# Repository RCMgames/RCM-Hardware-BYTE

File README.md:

# RCM-Hardware-BYTE
v2.3

* 1.25 by 1.25 inches, 31.75 by 31.75 millimeters
* 8 motors
* 8 servos
* battery monitoring
* I2C connector on QT PY
* runs on 3-11 volts

### Tested with the following types of ESP32 QT Py:
| Type of Qt Py | PlatformIO name | link to Adafruit |
| ------ | -------- | -------- |
| S3 with 2MB PSRAM |  adafruit_qtpy_esp32s3_n4r2   |  https://www.adafruit.com/product/5700   |
| S3 with 8Mb Flash |  adafruit_qtpy_esp32s3_nopsram   |  https://www.adafruit.com/product/5426   |
| S2 |  adafruit_qtpy_esp32s2   |  https://www.adafruit.com/product/5325  |

Look here for how to program it: https://github.com/RCMgames/RCMv2

Look here for more information and examples of robots: https://github.com/rcmgames

Want slightly smaller with a built in IMU? Look at the [Nibble](https://github.com/RCMgames/RCM-Hardware-Nibble)

## Options for purchasing

* [PCBWay link](https://www.pcbway.com/project/shareproject/RCMHardwareByte_v2_3_e23eec63.html) (PCBWay will give me a commission without increasing the price for you). (approximately $90 for 2 boards and manufacturing took a month).
* send the gerbers, bill of materials, and ComponentPlacement files to a PCB manufacturer of your choice (details you may be asked for: min hole 0.25mm, min track/spacing 5/5mil, thickness 1.0mm, 1 oz Cu outer 1.5 oz Cu inner)

## Components
Solder by hand to complete the assembly of your boards.
| part | links | quantity | notes |
| ----- | ----- | ----- | ----- |
| RCM BYTE circuit board | [options for purchasing](https://github.com/RCMgames/RCM-Hardware-BYTE/tree/main#options-for-purchasing) | 1 | |
| ESP32 QT Py | [compatible QT Py](https://github.com/RCMgames/RCM-Hardware-BYTE/tree/main#tested-with-the-following-types-of-esp32-qt-py) | 1 | |
| 2x8 female header pins | [this](https://www.digikey.com/en/products/detail/sullins-connector-solutions/PPPC042LFBN-RC/810244) or 2 strips of 8 | 1 | for motors |
| 7 female header pins | | 2 | for QT Py |
| 8 male header pins | | 4 | for servos |
| battery wires | JST RCY OR 9V battery snap | 1 | [Amazon JST RCY](https://www.amazon.com/dp/B00Z04QFN2/) |
| servo buck boost 5v 2A OR replace with a short length of wire| [Pololu](https://www.pololu.com/product/4085) | 2 | regulators are needed if you want to supply voltages above or below what servos can accept. There are 2 servo power buses, each with 4 servos. |

## Acknowledgements
* I would like to thank [PCBWay](https://www.pcbway.com/) for sponsoring prototyping runs of this project. PCBWay produces very nice boards, supports open source hardware, and gave me great support as I worked on this project. Special thanks to Liam!

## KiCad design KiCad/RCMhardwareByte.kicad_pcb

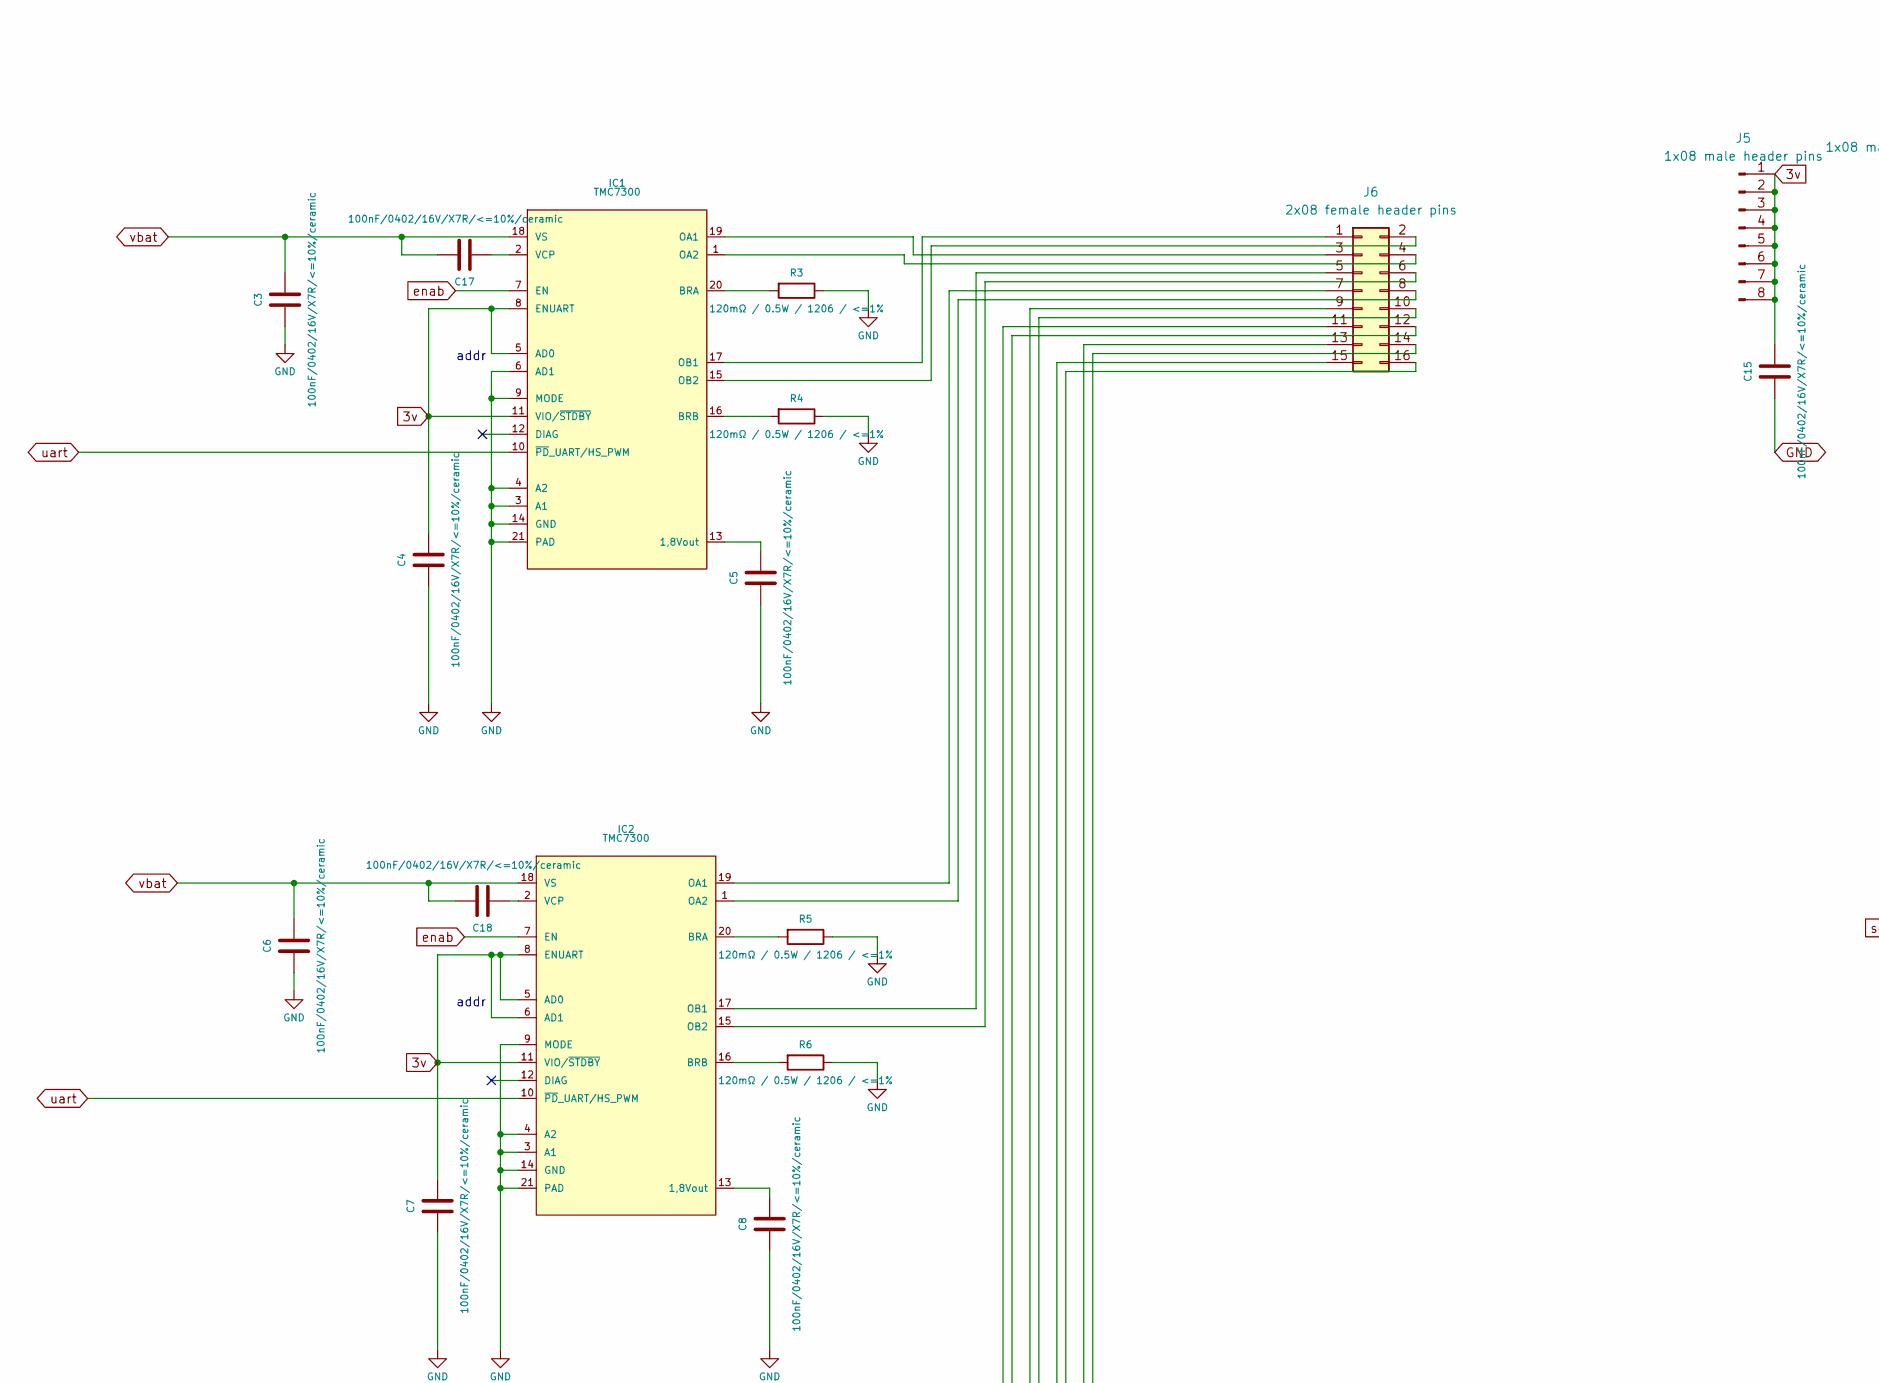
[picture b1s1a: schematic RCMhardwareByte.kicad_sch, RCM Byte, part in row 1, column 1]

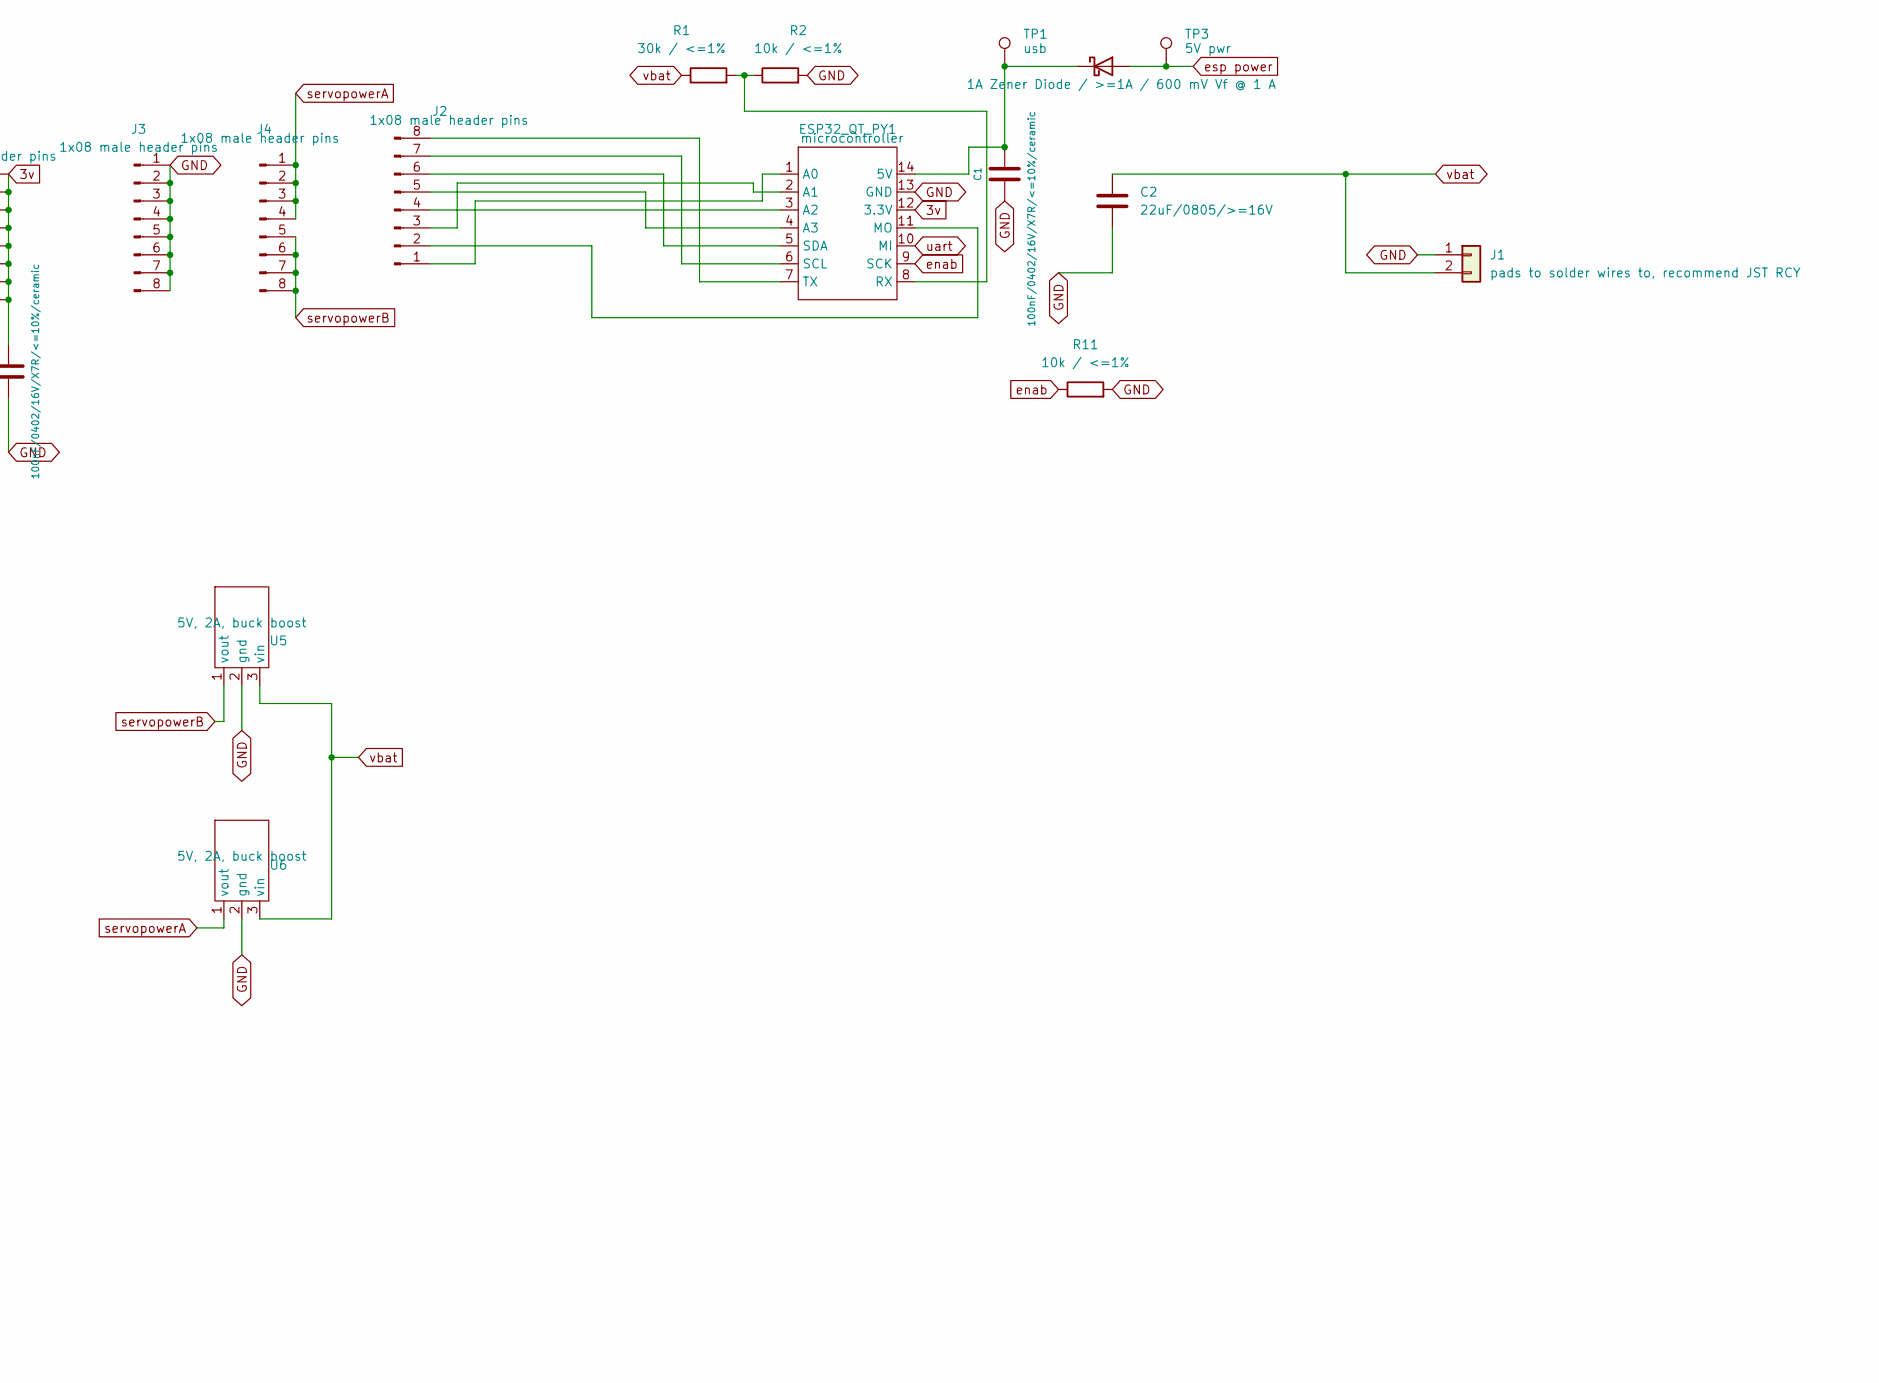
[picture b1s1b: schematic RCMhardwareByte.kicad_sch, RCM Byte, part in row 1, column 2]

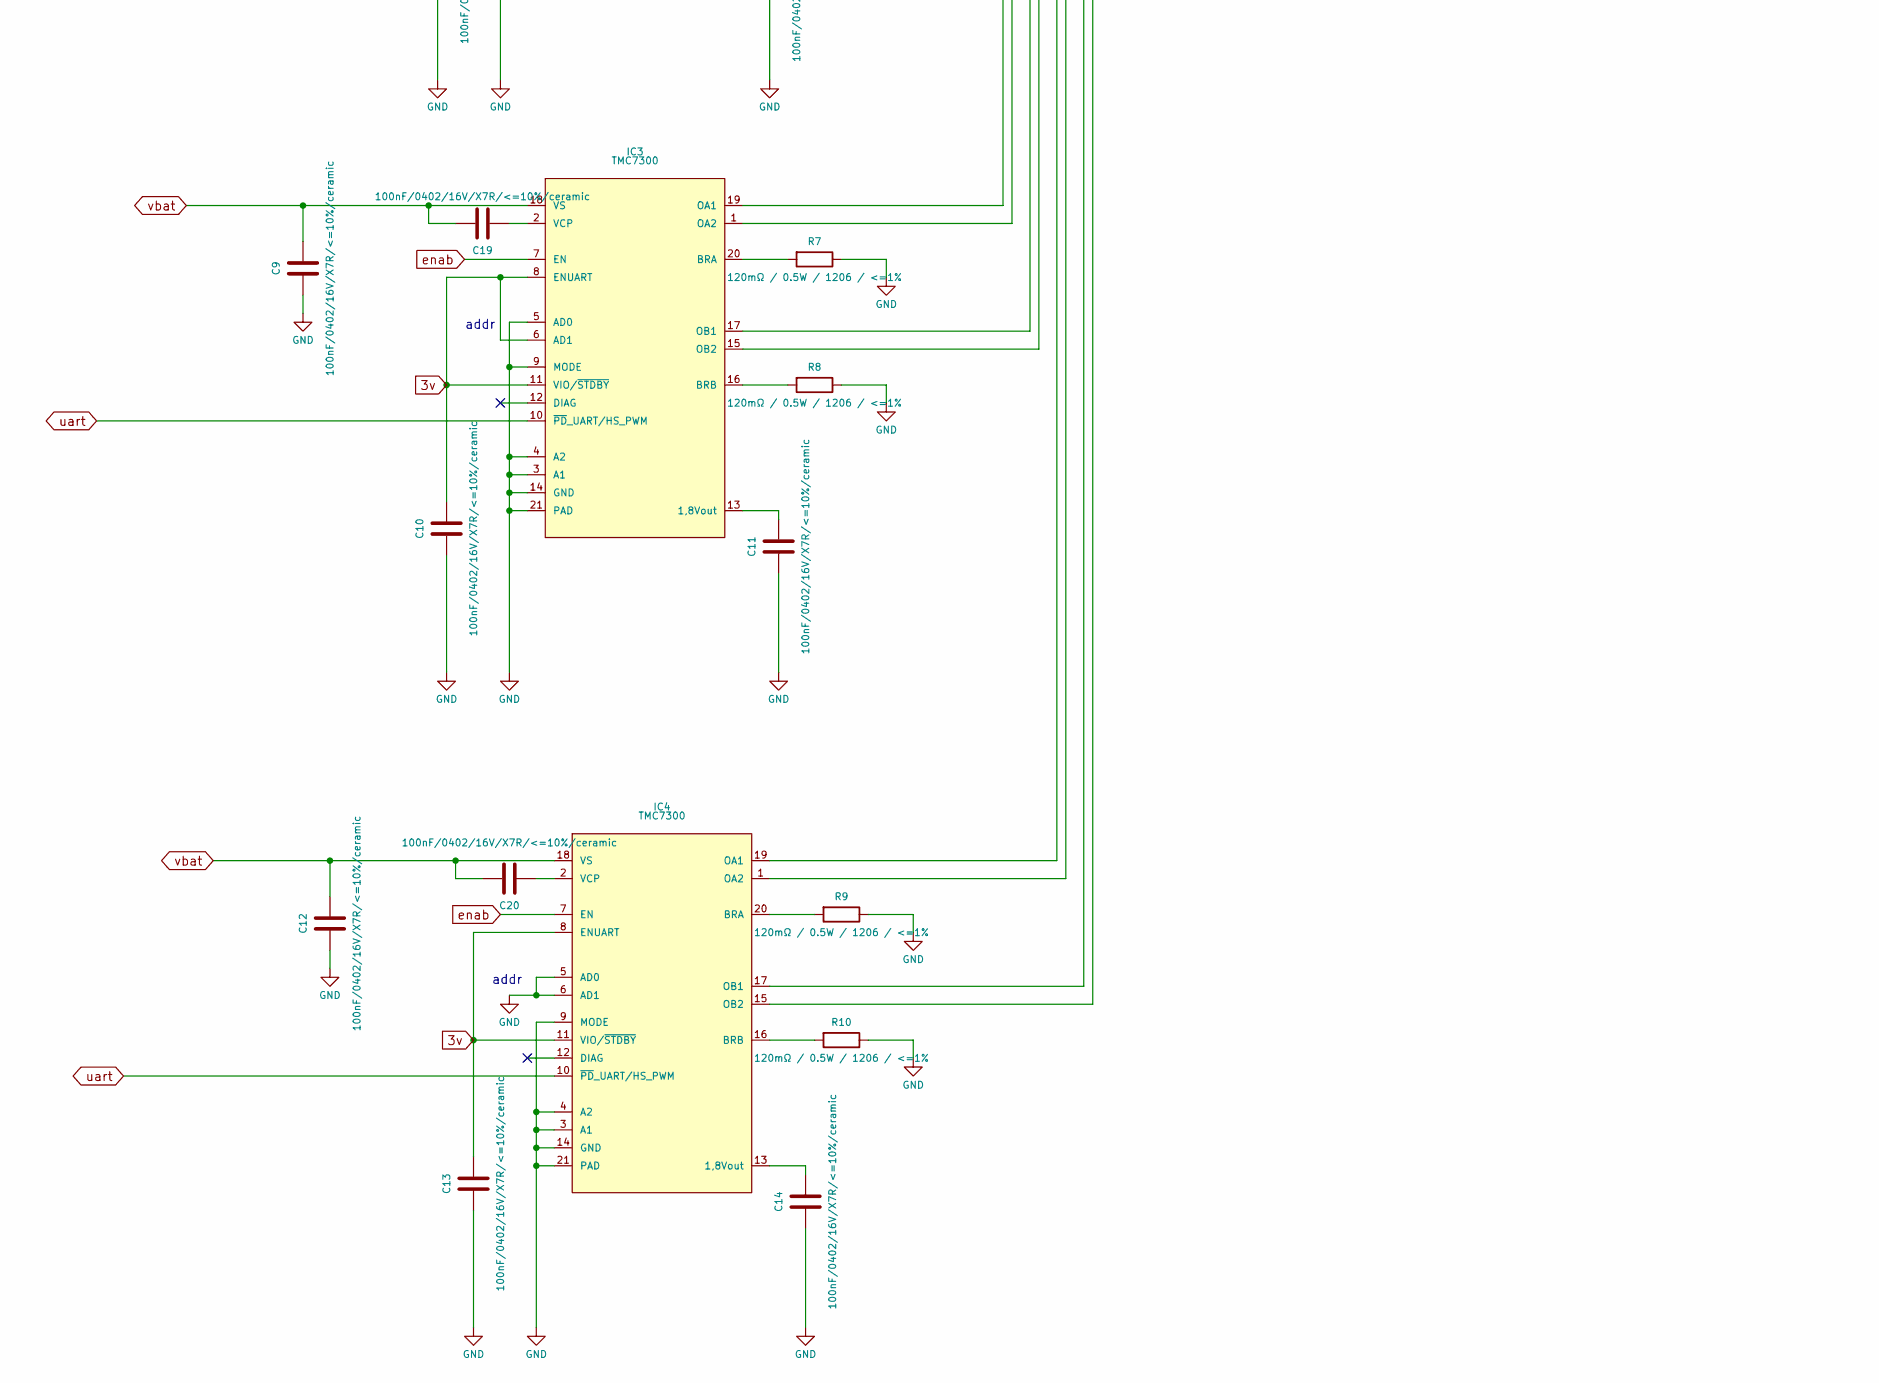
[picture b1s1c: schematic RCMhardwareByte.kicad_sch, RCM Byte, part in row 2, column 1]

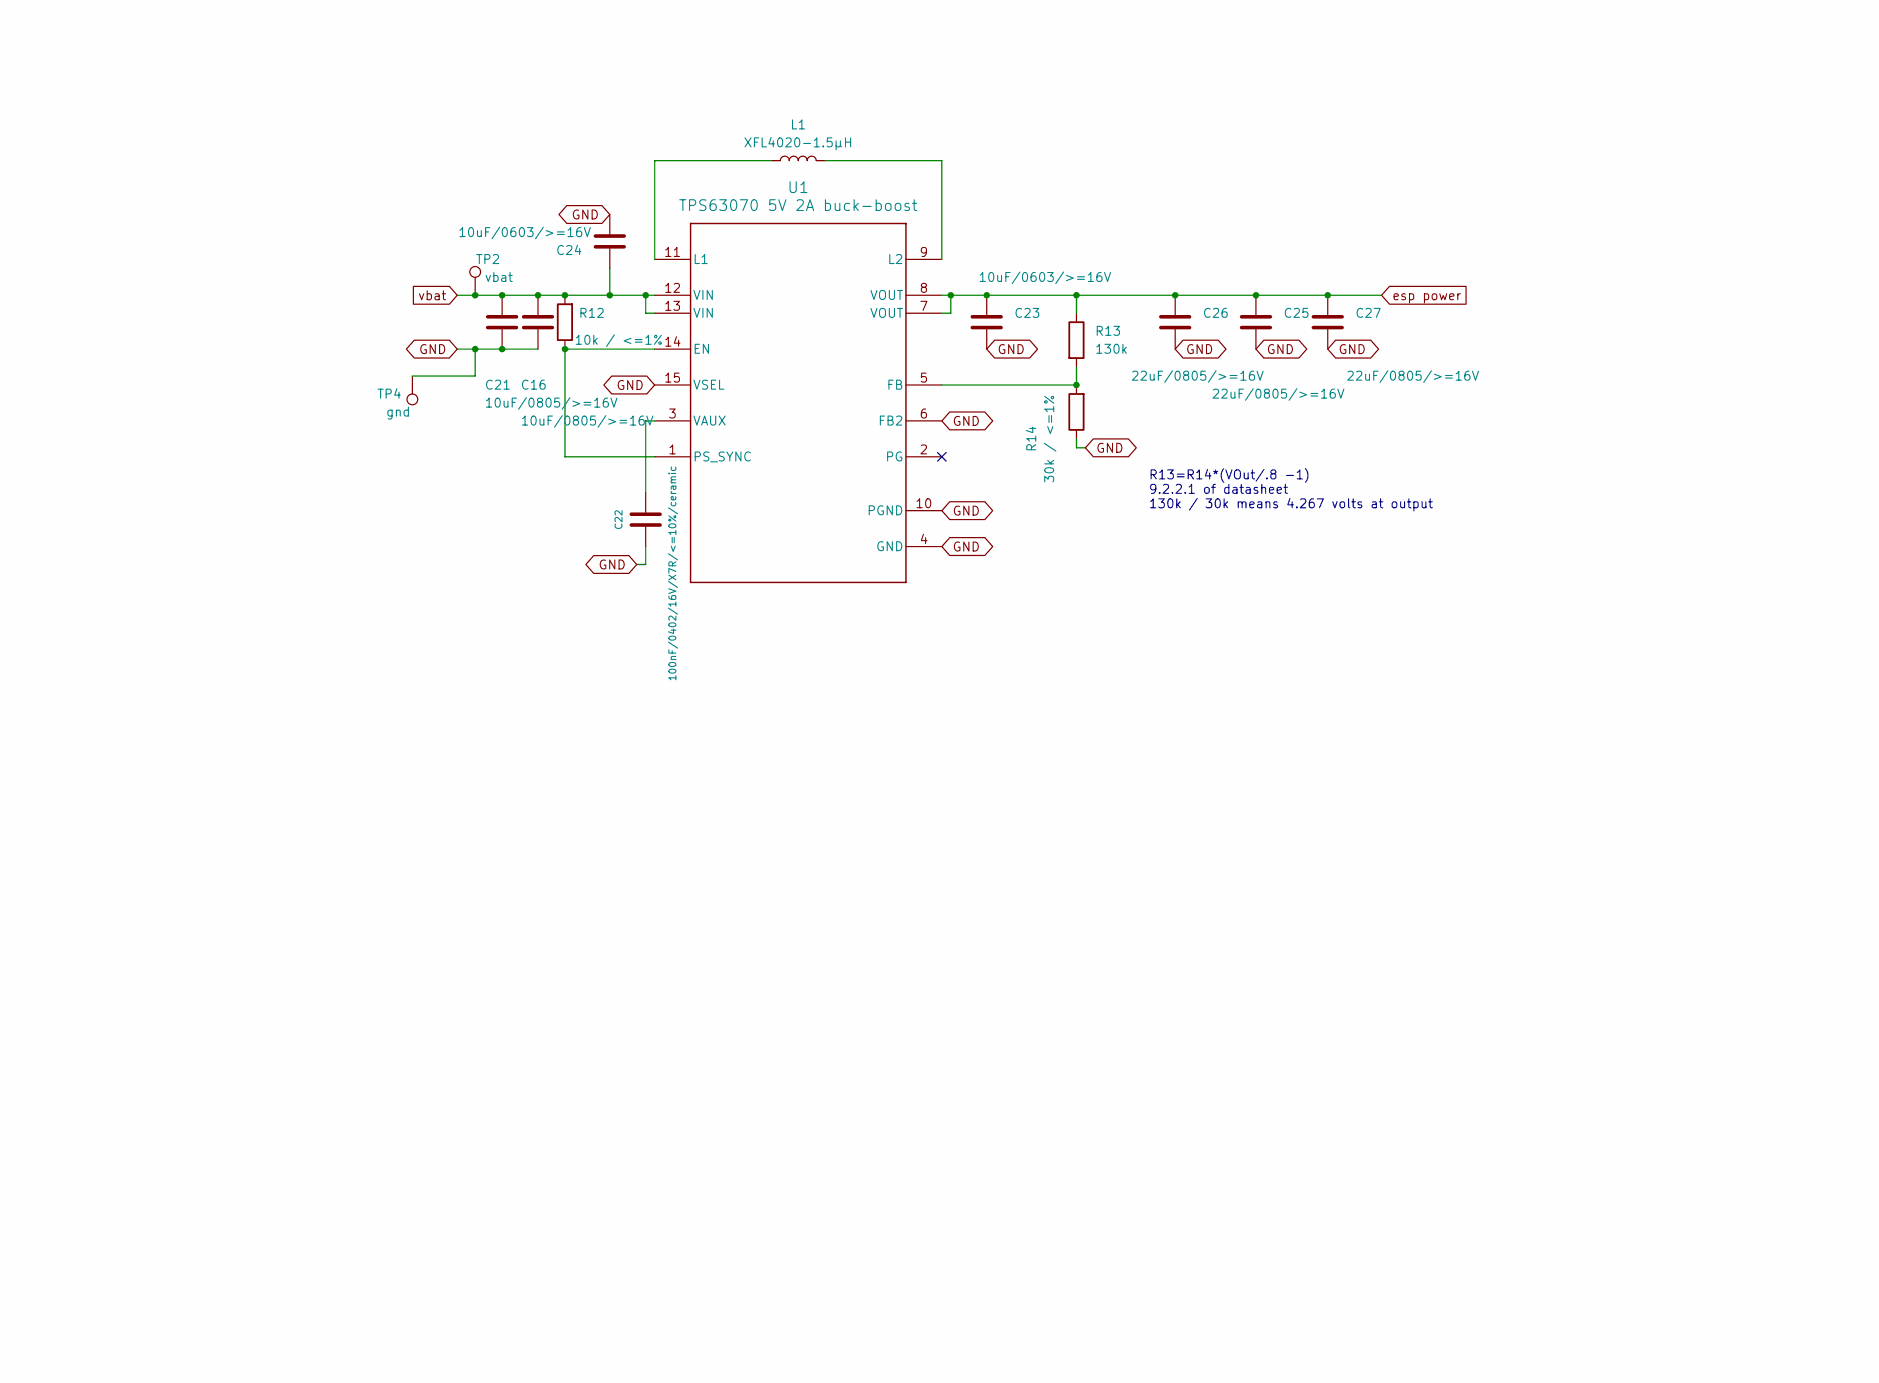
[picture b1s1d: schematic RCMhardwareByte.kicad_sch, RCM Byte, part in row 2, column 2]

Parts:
C1, C3, C4, C5, C6, C7, C8, C9, C10, C11, C12, C13, C14, C15, C17, C18, C19, C20, C22: 100nF/0402/16V/X7R/<=10%/ceramic; C_0402_1005Metric; mpn GMC04X7R104K50NT; digikey part # 4713-GMC04X7R104K50NTCT-ND
C2, C25, C26, C27: 22uF/0805/>=16V; C_0805_2012Metric; mpn GMC21X5R226M16NT; digikey part # 4713-GMC21X5R226M16NTCT-ND
C16, C21: 10uF/0805/>=16V; C_0805_2012Metric; mpn GMC21X7R106K16NT; digikey part # 4713-GMC21X7R106K16NTCT-ND
C23, C24: 10uF/0603/>=16V; C_0603_1608Metric; mpn GMC10X5R106M25NT; digikey part # 4713-GMC10X5R106M25NTCT-ND
D1: 1A Zener Diode / >=1A / 600 mV Vf @ 1 A; D_SOD-323; mpn GDB5818WS; digikey part # 4786-GDB5818WSCT-ND
ESP32_QT_PY1: microcontroller; ESP32 QT PY
IC1, IC2, IC3, IC4: TMC7300; QFN-20-1EP_3x3mm_P0.4mm_EP1.65x1.65mm; mpn TMC7300-LA-T; digikey part # 175-TMC7300-LA-TCT-ND
J1: pads to solder wires to, recommend JST RCY; battery wires
J2, J3, J4, J5: 1x08 male header pins; servo pin column
J6: 2x08 female header pins; PinSocket_2x08_P2.54mm_Vertical
L1: XFL4020-1.5μH; L_Coilcraft_XxL4020; mpn XFL4020-152MEC; digikey part # 2457-XFL4020-152MEC-ND
R1, R14: 30k / <=1%; R_0402_1005Metric; mpn CRG0402F30K; digikey part # 1712-CRG0402F30KCT-ND
R2, R11, R12: 10k / <=1%; R_0402_1005Metric; mpn CRG0402F10K; digikey part # A121528CT-ND
R3, R4, R5, R6, R7, R8, R9, R10: 120mΩ / 0.5W / 1206 / <=1%; R_1206_3216Metric; mpn CRL1206-FW-R120ELF; digikey part # CRL1206-FW-R120ELFCT-ND
R13: 130k; R_0402_1005Metric; mpn CPF0402B130KE; digikey part # A119923CT-ND
TP1: usb; TestPoint_Pad_D1.5mm; mpn n/a; digikey part # n/a
TP2: vbat; TestPoint_Pad_D1.5mm; mpn n/a; digikey part # n/a
TP3: 5V pwr; TestPoint_Pad_D1.5mm; mpn n/a; digikey part # n/a
TP4: gnd; TestPoint_Pad_D1.5mm; mpn n/a; digikey part # n/a
U1: TPS63070 5V 2A buck-boost; TPS630701RNMR; mpn TPS63070RNMR; digikey part # 296-44874-1-ND
U5, U6: 5V, 2A, buck boost; pololu4085

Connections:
3v: C4.1, C7.1, C10.1, C13.1, C15.1, ESP32_QT_PY1.12 (3.3V), IC1.5 (AD0), IC1.8 (ENUART), IC1.11 (VIO/~STDBY), IC2.5 (AD0), IC2.6 (AD1), IC2.8 (ENUART), IC2.11 (VIO/~STDBY), IC3.6 (AD1), IC3.8 (ENUART), IC3.11 (VIO/~STDBY), IC4.8 (ENUART), IC4.11 (VIO/~STDBY), J5.1, J5.2, J5.3, J5.4, J5.5, J5.6, J5.7, J5.8
GND: C1.2, C2.2, C3.2, C4.2, C5.2, C6.2, C7.2, C8.2, C9.2, C10.2, C11.2, C12.2, C13.2, C14.2, C15.2, C16.2, C21.2, C22.2, C23.2, C24.2, C25.2, C26.2, C27.2, ESP32_QT_PY1.13 (GND), IC1.3 (A1), IC1.4 (A2), IC1.6 (AD1), IC1.9 (MODE), IC1.14 (GND), IC1.21 (PAD), IC2.3 (A1), IC2.4 (A2), IC2.9 (MODE), IC2.14 (GND), IC2.21 (PAD), IC3.3 (A1), IC3.4 (A2), IC3.5 (AD0), IC3.9 (MODE), IC3.14 (GND), IC3.21 (PAD), IC4.3 (A1), IC4.4 (A2), IC4.5 (AD0), IC4.6 (AD1), IC4.9 (MODE), IC4.14 (GND), IC4.21 (PAD), J1.1, J3.1, J3.2, J3.3, J3.4, J3.5, J3.6, J3.7, J3.8, R2.2, R3.1, R4.1, R5.1, R6.1, R7.1, R8.1, R9.1, R10.1, R11.2, R14.1, TP4.1, U1.4 (GND), U1.6 (FB2), U1.10 (PGND), U1.15 (VSEL), U5.2 (gnd), U6.2 (gnd)
unnamed: C1.1, D1.1 (K), ESP32_QT_PY1.14 (5V), TP1.1
unnamed: ESP32_QT_PY1.1 (A0), J2.1
unnamed: ESP32_QT_PY1.2 (A1), J2.3
unnamed: ESP32_QT_PY1.3 (A2), J2.4
unnamed: ESP32_QT_PY1.4 (A3), J2.5
unnamed: ESP32_QT_PY1.11 (MO), J2.2
unnamed: ESP32_QT_PY1.8 (RX), R1.2, R2.1
unnamed: ESP32_QT_PY1.6 (SCL), J2.7
unnamed: ESP32_QT_PY1.5 (SDA), J2.6
unnamed: ESP32_QT_PY1.7 (TX), J2.8
unnamed: C5.1, IC1.13 (1,8Vout)
unnamed: IC1.20 (BRA), R3.2
unnamed: IC1.16 (BRB), R4.2
unnamed: IC1.19 (OA1), J6.3
unnamed: IC1.1 (OA2), J6.4
unnamed: IC1.17 (OB1), J6.1
unnamed: IC1.15 (OB2), J6.2
unnamed: C17.2, IC1.2 (VCP)
unnamed: C8.1, IC2.13 (1,8Vout)
unnamed: IC2.20 (BRA), R5.2
unnamed: IC2.16 (BRB), R6.2
unnamed: IC2.19 (OA1), J6.7
unnamed: IC2.1 (OA2), J6.8
unnamed: IC2.17 (OB1), J6.5
unnamed: IC2.15 (OB2), J6.6
unnamed: C18.2, IC2.2 (VCP)
unnamed: C11.1, IC3.13 (1,8Vout)
unnamed: IC3.20 (BRA), R7.2
unnamed: IC3.16 (BRB), R8.2
unnamed: IC3.19 (OA1), J6.11
unnamed: IC3.1 (OA2), J6.12
unnamed: IC3.17 (OB1), J6.9
unnamed: IC3.15 (OB2), J6.10
unnamed: C19.2, IC3.2 (VCP)
unnamed: C14.1, IC4.13 (1,8Vout)
unnamed: IC4.20 (BRA), R9.2
unnamed: IC4.16 (BRB), R10.2
unnamed: IC4.19 (OA1), J6.15
unnamed: IC4.1 (OA2), J6.16
unnamed: IC4.17 (OB1), J6.13
unnamed: IC4.15 (OB2), J6.14
unnamed: C20.2, IC4.2 (VCP)
unnamed: R12.1, U1.1 (PS_SYNC), U1.14 (EN)
unnamed: R13.2, R14.2, U1.5 (FB)
unnamed: L1.1, U1.11 (L1)
unnamed: L1.2, U1.9 (L2)
unnamed: C22.1, U1.3 (VAUX)
enab: ESP32_QT_PY1.9 (SCK), IC1.7 (EN), IC2.7 (EN), IC3.7 (EN), IC4.7 (EN), R11.1
esp power: C23.1, C25.1, C26.1, C27.1, D1.2 (A), R13.1, TP3.1, U1.7 (VOUT), U1.8 (VOUT)
servopowerA: J4.1, J4.2, J4.3, J4.4, U6.1 (vout)
servopowerB: J4.5, J4.6, J4.7, J4.8, U5.1 (vout)
uart: ESP32_QT_PY1.10 (MI), IC1.10 (~PD_UART/HS_PWM), IC2.10 (~PD_UART/HS_PWM), IC3.10 (~PD_UART/HS_PWM), IC4.10 (~PD_UART/HS_PWM)
vbat: C2.1, C3.1, C6.1, C9.1, C12.1, C16.1, C17.1, C18.1, C19.1, C20.1, C21.1, C24.1, IC1.18 (VS), IC2.18 (VS), IC3.18 (VS), IC4.18 (VS), J1.2, R1.1, R12.2, TP2.1, U1.12 (VIN), U1.13 (VIN), U5.3 (vin), U6.3 (vin)

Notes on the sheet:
addr
R13=R14*(VOut/.8 -1) 9.2.2.1 of datasheet 130k / 30k means 4.267 volts at output

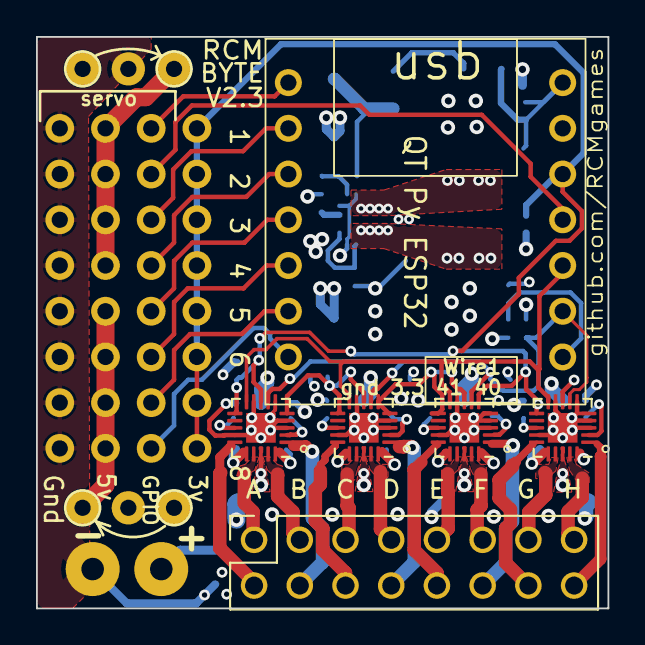
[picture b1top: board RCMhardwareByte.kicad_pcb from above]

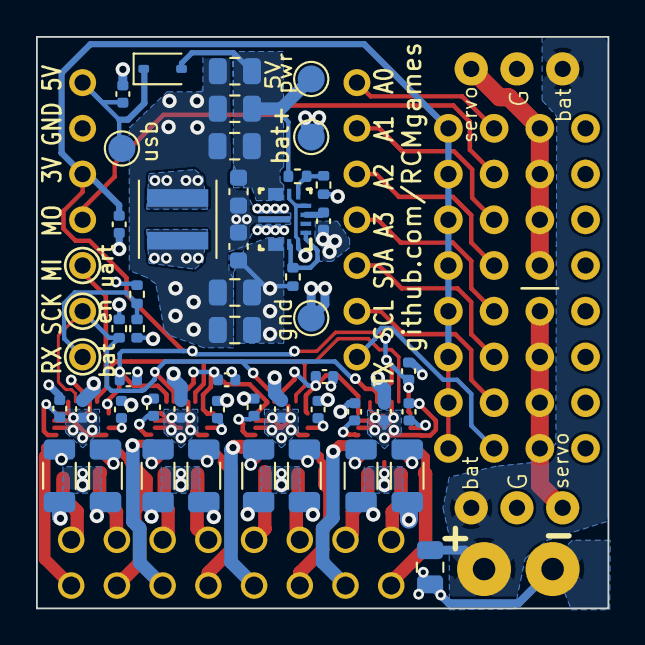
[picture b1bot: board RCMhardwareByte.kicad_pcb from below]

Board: 4 copper layers, 31.8 x 31.8 mm, 61 parts (48 on the bottom side), 55 nets.

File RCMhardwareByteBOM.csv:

"Reference","Value","Footprint","Datasheet","Manufacturer","Package","digikey part #","link","mount_type","mpn","Qty"
"C1, C3-C15, C17-C20, C22","100nF/0402/>=16V/X7R","Capacitor_SMD:C_0402_1005Metric","~","TDK Corporation","0402","445-5932-1-ND","https://www.digikey.com/en/products/detail/tdk-corporation/C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","smt","C1005X7R1H104K050BB","19"
"C2, C26, C27","22uF/0805/>=16V","Capacitor_SMD:C_0805_2012Metric","~","Cal-Chip Electronics, Inc.","0805","4713-GMC21X5R226M16NTCT-ND","https://www.digikey.cn/en/products/detail/cal-chip-electroni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","smt","GMC21X5R226M16NT","3"
"C16, C21","10uF/0805/>=16V","Capacitor_SMD:C_0805_2012Metric","~","TDK Corporation","0805","445-7611-1-ND","https://www.digikey.cn/en/products/detail/tdk-corporation/C2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","smt","C2012X6S1C106K125AC","2"
"C23, C24","10uF/0603/>=16V/Low ESL","Capacitor_SMD:C_0603_1608Metric","~","TDK Corporation","0603","445-9015-1-ND","https://www.digikey.com/en/products/detail/tdk-corporation/C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","smt","C1608X5R1E106M080AC","2"
"D1","1A Diode, Vf 500mV","Diode_SMD:D_SOD-323","~","any","D_SOD-323","NSVR1020MW2T1GOSCT-ND","https://www.digikey.com/en/products/detail/onsemi/NSVR1020MW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","smt","NSVR1020MW2T1G","1"
"ESP32_QT_PY1","microcontroller","!RCMhardware footprints:ESP32 QT PY","~","Adafruit","tht","","https://www.digikey.com/en/products/detail/adafruit-industri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","do not place or purchase for PCB assembly","","1"
"IC1-IC4","TMC7300","!RCMhardware footprints:QFN-20-1EP_3x3mm_P0.4mm_EP1.65x1.65mm","https://www.analog.com/media/en/technical-documentation/data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","Analog Devices","QFN-20-1EP_3x3mm_P0.4mm_EP1.65x1.65mm","175-TMC7300-LA-TCT-ND","https://www.digikey.com/en/products/detail/analog-devices-in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","smt","TMC7300-LA-T","4"
"J1","pads to solder wires to, recommend JST RCY","!RCMhardware footprints:battery wires","~","","tht","","https://www.amazon.com/dp/B00Z04QFN2/","do not place or purchase for PCB assembly","","1"
"J2-J5","1x08 male header pins","!RCMhardware footprints:servo pin column","~","","tht","","","do not place or purchase for PCB assembly","","4"
"J6","2x08 female header pins","!RCMhardware footprints:PinSocket_2x08_P2.54mm_Vertical","~","","tht","","https://www.digikey.com/en/products/detail/sullins-connector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","do not place or purchase for PCB assembly","","1"
"L1","XFL4020-1.5μH","!RCMhardware footprints:L_Coilcraft_XxL4020","~","Coilcraft","1616","2457-XFL4020-152MEC-ND","https://www.digikey.com/en/products/detail/coilcraft/XFL4020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","smt","XFL4020-152MEC","1"
"R1","49.9k or 50k","Resistor_SMD:R_0402_1005Metric","~","Bourns Inc.","0402","118-CRT0402-BY-4992GLFCT-ND","https://www.digikey.com/en/products/detail/bourns-inc/CRT040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","smt","CRT0402-BY-4992GLF","1"
"R2, R11, R12","10k","Resistor_SMD:R_0402_1005Metric","~","Bourns Inc.","0402","CR0402-FX-1002GLFCT-ND","https://www.digikey.com/en/products/detail/bourns-inc/CR0402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","smt","CR0402-FX-1002GLF","3"
"R3-R10","120mΩ / 0.5W / 1206 / <=1%","Resistor_SMD:R_1206_3216Metric","~","Bourns Inc.","1206","CRL1206-FW-R120ELFCT-ND","https://www.digikey.com/en/products/detail/bourns-inc/CRL120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","smt","CRL1206-FW-R120ELF","8"
"TP1-TP4","TestPoint","TestPoint:TestPoint_Pad_D1.5mm","~","n/a","n/a","","","do not place or purchase for PCB assembly","","4"
"U1","TPS630701RNMR 5V 2A buck-boost","!RCMhardware footprints:TPS630701RNMR","https://www.ti.com/lit/ds/symlink/tps63070.pdf","Texas Instruments","15-VQFN-HR (3x2.5)","296-47298-1-ND","https://www.digikey.com/en/products/detail/texas-instruments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","smt","TPS630701RNMR","1"
"U5, U6","5V, 2A, buck boost","!RCMhardware footprints:pololu4085","~","Pololu","tht","","https://www.pololu.com/product/4085","do not place or purchase for PCB assembly","","2"

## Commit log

2024-03-21 organize files
2024-04-03 upload v2.1
2024-04-03 add pictures
2024-04-03 Update LICENSE
2024-04-03 add 3d files
2024-04-03 add 3d cad
2024-04-18 v2.2.0
2024-05-09 v2.3.0
2024-05-09 add renders
2024-07-30 fix typo
